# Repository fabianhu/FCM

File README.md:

FCM
===

FCM Flight Controller Firmware

Contents:

	Bootloader - the bootloader AVR32 project
	
	doc -  the main documentation folder -> read FCM Manual.pdf.
	
	hardware - here are the hardware sources. "hexa2wide" is our board. The actual physically produced board is under versions. This is the next release!
	
	software - the FCM copter control firmware main project

Size & weight:

	45 x 27 x 8 mm
	10 g

CPU:

	AVR32 UC3B0256
	32 bit
	48MHz

Sensors:

	Gyroscope (3 axis)
	Accelometer (3 axis)
	Magnetometer (3 axis)
	Barometer

Interfaces:

	4x PPM input or
	Receiver serial input for SPEKTRUM and HoTT or
	Receiver PPM sum signal input
	2x extra TTL USART (for Bluetooth, GPS, Telemetry etc.)
	6x PPM output for speed controllers (SimonK firmware recommended)
	optocoupler for 5 PPM outputs (placement variant)
	Pulse input for ultrasonic distance measurement
	USB for configuration and updates

Software features:

	FabOS32 RTOS
	Quaternion based attitude control
	Altitude hold
	Any copter configuration via mixing matrix
	RC compatibility
	HoTT SUMD receiver signal
	SPEKTRUM sattelite receiver signal
	4-channel "any RX" classic mode
	PPM sum signal
	USB Bootloader
	GPS integration with waypoint processing and return-to-home
	Throw to start
	
Telemetry

	HoTT telemetry with settings menue
	Bluetooth telemetry with settings menue, Attitude and graph display
	MAVlink prepared
	PID setting via extra RC analog channels

Software is "closed source" = all own code with minor extensions with LGPL
	Software is now open-sourced under GPL V3

Visit also the projects:
	FCM-android and
	FCM-Manager

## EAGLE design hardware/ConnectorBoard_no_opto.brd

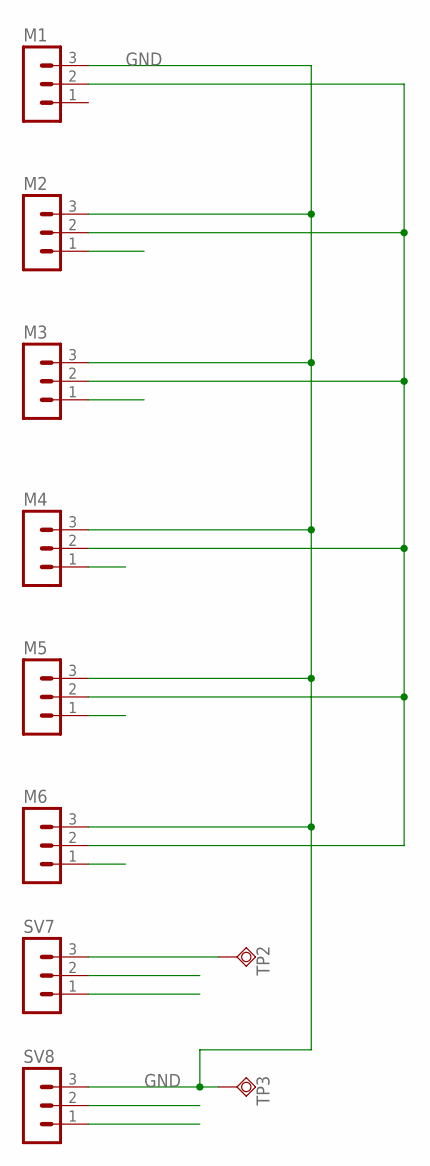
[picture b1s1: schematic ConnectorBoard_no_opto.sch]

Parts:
M1, M2, M3, M4, M5, M6: MA03-1
SV7, SV8: MA03-1
TP2, TP3: TPSQTP14SQ; TP14SQ

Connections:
GND: M1.3, M2.3, M3.3, M4.3, M5.3, M6.3, SV8.3, TP3.TP
unnamed: M1.2, M2.2, M3.2, M4.2, M5.2, M6.2
unnamed: SV7.3, TP2.TP

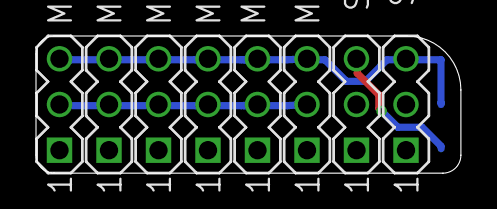
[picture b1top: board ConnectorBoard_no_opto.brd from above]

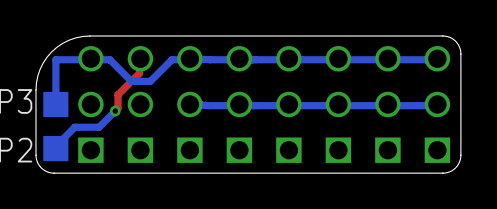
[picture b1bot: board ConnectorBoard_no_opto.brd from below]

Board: 2 copper layers, 23.6 x 7.6 mm, 10 parts (2 on the bottom side), 3 nets.

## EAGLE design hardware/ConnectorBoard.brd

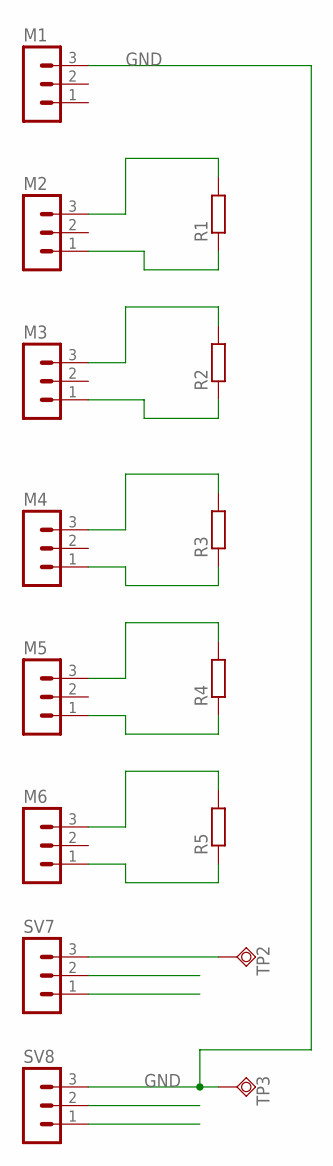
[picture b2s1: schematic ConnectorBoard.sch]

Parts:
M1, M2, M3, M4, M5, M6: MA03-1
R1, R2, R3, R4, R5: R-EU_R0402; R0402
SV7, SV8: MA03-1
TP2, TP3: TPSQTP14SQ; TP14SQ

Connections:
GND: M1.3, SV8.3, TP3.TP
unnamed: M3.3, R2.2
unnamed: M2.3, R1.2
unnamed: M2.1, R1.1
unnamed: M3.1, R2.1
unnamed: M4.3, R3.2
unnamed: M4.1, R3.1
unnamed: M5.3, R4.2
unnamed: M5.1, R4.1
unnamed: M6.3, R5.2
unnamed: M6.1, R5.1
unnamed: SV7.3, TP2.TP

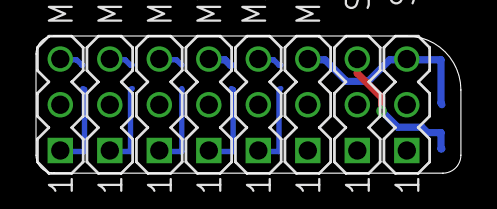
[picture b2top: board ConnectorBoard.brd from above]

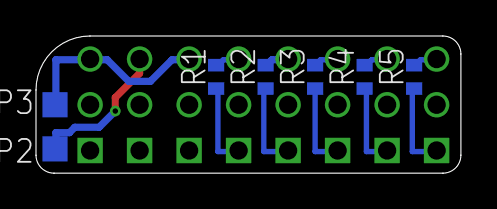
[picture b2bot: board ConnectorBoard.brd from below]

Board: 2 copper layers, 23.6 x 7.6 mm, 15 parts (7 on the bottom side), 12 nets.

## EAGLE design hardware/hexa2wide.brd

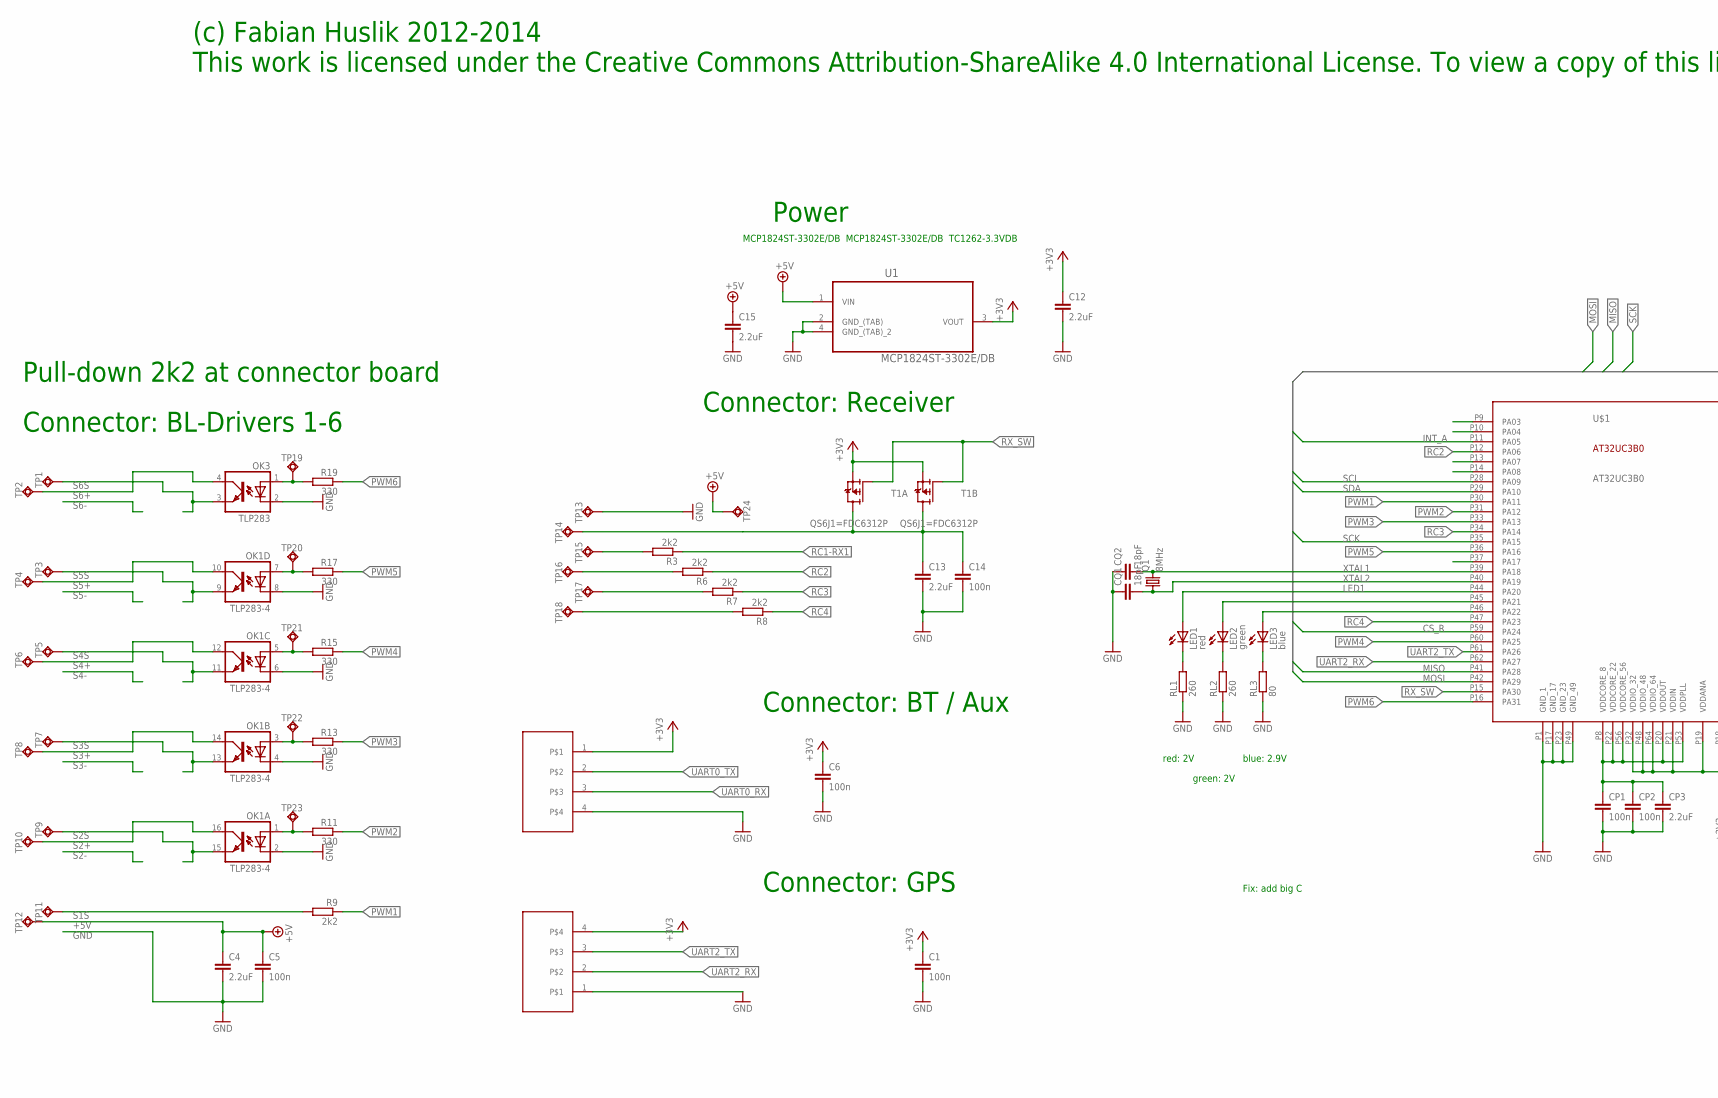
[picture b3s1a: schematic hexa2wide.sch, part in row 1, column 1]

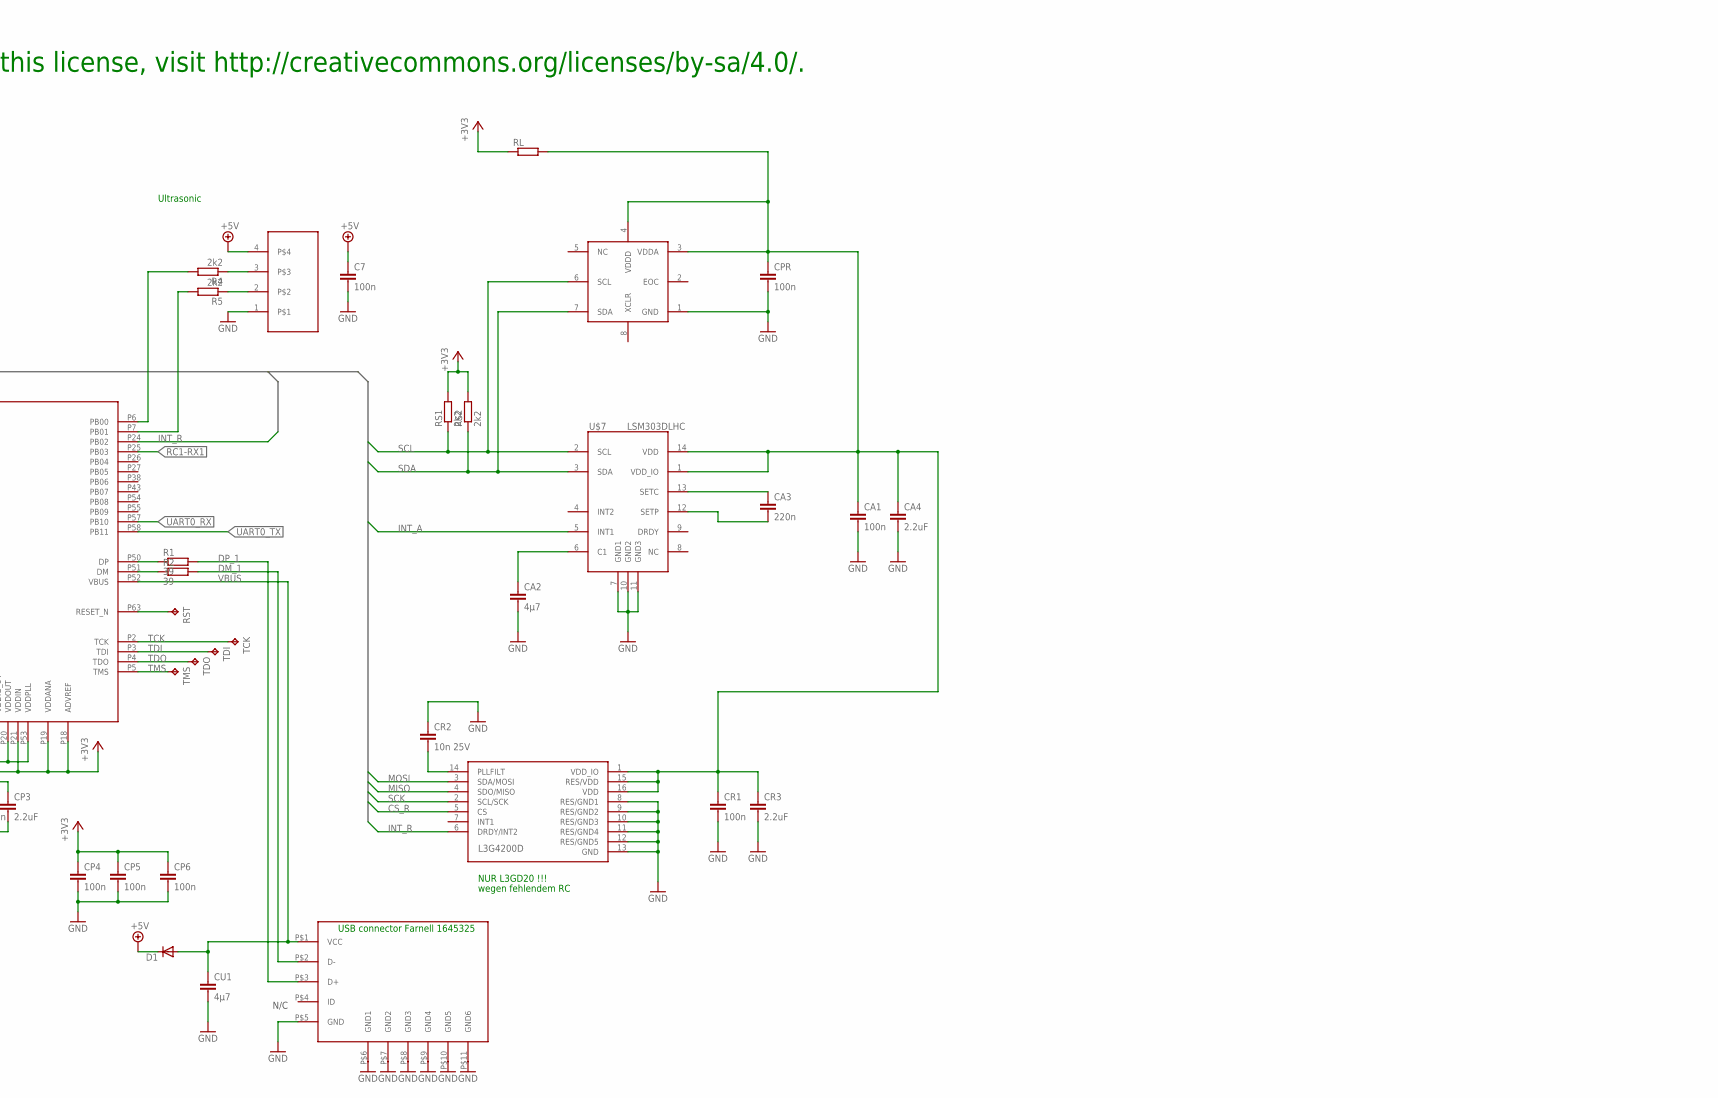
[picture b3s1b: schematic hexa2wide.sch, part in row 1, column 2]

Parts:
C1, C5, C6, C7, C14: 100n; C0402; MPN MCCA000050
C4, C12, C13, C15: 2.2uF; C0603K; MPN GRM188R61C225KE15D
CA1: 100n; C0402; MPN MCCA000050
CA2: 4µ7; C0805; MPN GRM219R61C475KE15D
CA3: 220n; C0402; MPN C0402C224K9PACTU
CA4: 2.2uF; C0603K; MPN GRM188R61C225KE15D
CP1, CP2, CP4, CP5, CP6: 100n; C0402; MPN MCCA000050
CP3: 2.2uF; C0603K; MPN GRM188R61C225KE15D
CPR: 100n; C0402; MPN MCCA000050
CQ1, CQ2: 18pF; C0402; MPN C0402C180J5GACTU
CR1: 100n; C0402; MPN MCCA000050
CR2: 10n 25V; C0402; MPN MCCA000076
CR3: 2.2uF; C0603K; MPN GRM188R61C225KE15D
CU1: 4µ7; C0805; MPN GRM219R61C475KE15D
D1: DIODE-MICROMELF-R; MICROMELF-R
LED1: red; CHIP-LED0603; MPN ASMT-RR45-AQ902
LED2: green; CHIP-LED0603; MPN ASMT-RF45-AN002
LED3: blue; CHIP-LED0603; MPN SMLE12BC7TT86Q
OK1: TLP283-4; MINI-FLAT-16; MPN ACPL-247-500E
OK3: TLP283; MINI-FLAT-4; MPN ACPL-217-500E
Q1: 8MHz; CTS406; MPN ABMM2-8.000MHZ-E2-T
R1, R2: 39; R0402; MPN CRCW040239R0FKEAHP
R3, R4, R5, R6, R7, R8, R9: 2k2; R0402; MPN CRCW040210K5FKED
R11, R13, R15, R17, R19: 330; R0402; MPN MCMR04X331 JTL
RL: R-EU_R0603; R0603; MPN 74279266
RL1, RL2: 260; R0402; MPN CRCW0402604RFKED
RL3: 80; R0402; MPN ERJ2RKF8062X
RS1, RS2: 2k2; R0402; MPN CRCW040210K5FKED
RST: TPB1,27; B1,27
T1: QS6J1=FDC6312P; SUPERSOT-6; MPN FDC6312P
TCK: TPB1,27; B1,27
TDI: TPB1,27; B1,27
TDO: TPB1,27; B1,27
TMS: TPB1,27; B1,27
TP1, TP2, TP3, TP4, TP5, TP6, TP7, TP8, TP9, TP10, TP11, TP12, TP13, TP14, TP15, TP16, TP17, TP18: TPSQTP16SQ; TP16SQ
TP19, TP20, TP21, TP22, TP23, TP24: TPSQTP10SQ; TP10SQ
U1: MCP1824ST-3302E/DB; SOT230P700X180-4N; MPN MCP1824ST-3302E/DB
U$1: AT32UC3B0; JEDEC_MS-026; MPN AT32UC3B0256-A2UT
U$4: UBB_MICRO_HIROSE; USB_MICRO; MPN ZX62-B-5PA(11)
U$5: L3G4200DHAND; LGA16_HAND; MPN L3GD20
U$7: LSM303HAND; LGA14_HAND; MPN LSM303DLHC
U$9: BMP085
U$10, U$11, U$12: 4WIRE_CONN; 4WIRE_PIN

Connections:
1V6: CP1.1, CP2.1, CP3.1, U$1.P8 (VDDCORE_8), U$1.P20 (VDDOUT), U$1.P22 (VDDCORE_22), U$1.P53 (VDDPLL), U$1.P56 (VDDCORE_56)
+3V3: C1.1, C6.1, C12.1, CP4.1, CP5.1, CP6.1, RL.1, RS1.2, RS2.2, T1.P$2 (S), T1.P$5 (S), U1.3 (VOUT), U$1.P18 (ADVREF), U$1.P19 (VDDANA), U$1.P21 (VDDIN), U$1.P32 (VDDIO_32), U$1.P48 (VDDIO_48), U$1.P64 (VDDIO_64), U$10.4, U$11.1
+5V: C4.1, C5.1, C7.1, C15.1, D1.C, TP12.TP, TP24.TP, U1.1 (VIN), U$12.4
CS_R: U$1.P59 (PA24), U$5.5 (CS)
DM: R2.1, U$1.P51 (DM)
DM_1: R2.2, U$4.P$2 (D-)
DP: R1.1, U$1.P50 (DP)
DP_1: R1.2, U$4.P$3 (D+)
GND: C1.2, C4.2, C5.2, C6.2, C7.2, C12.2, C13.2, C14.2, C15.2, CA1.2, CA2.2, CA4.2, CP1.2, CP2.2, CP3.2, CP4.2, CP5.2, CP6.2, CPR.2, CQ1.1, CQ2.1, CR1.2, CR2.1, CR3.2, CU1.2, OK1.2 (C), OK1.4 (C), OK1.6 (C), OK1.8 (C), OK3.2 (C), RL1.1, RL2.1, RL3.1, TP13.TP, U1.2 (GND_(TAB)), U1.4 (GND_(TAB)_2), U$1.P1 (GND_1), U$1.P17 (GND_17), U$1.P23 (GND_23), U$1.P49 (GND_49), U$4.P$5 (GND), U$4.P$6 (GND1), U$4.P$7 (GND2), U$4.P$8 (GND3), U$4.P$9 (GND4), U$4.P$10 (GND5), U$4.P$11 (GND6), U$5.8 (RES/GND1), U$5.9 (RES/GND2), U$5.10 (RES/GND3), U$5.11 (RES/GND4), U$5.12 (RES/GND5), U$5.13 (GND), U$7.7 (GND1), U$7.10 (GND2), U$7.11 (GND3), U$9.1 (GND), U$10.1, U$11.4, U$12.1
INT_A: U$1.P11 (PA05), U$7.5 (INT1)
INT_R: U$1.P24 (PB02), U$5.6 (DRDY/INT2)
LED1: LED1.A, U$1.P44 (PA20)
MISO: U$1.P41 (PA28), U$5.4 (SDO/MISO)
MOSI: U$1.P42 (PA29), U$5.3 (SDA/MOSI)
unnamed: LED1.C, RL1.2
unnamed: RST.TP, U$1.P63 (RESET_N)
unnamed: CA3.1, U$7.13 (SETC)
unnamed: LED2.C, RL2.2
unnamed: LED3.C, RL3.2
unnamed: LED2.A, U$1.P45 (PA21)
unnamed: LED3.A, U$1.P46 (PA22)
unnamed: CR2.2, U$5.14 (PLLFILT)
unnamed: CA2.1, U$7.6 (C1)
unnamed: CA3.2, U$7.12 (SETP)
unnamed: R3.2, TP15.TP
unnamed: C13.1, C14.1, T1.P$4 (D), T1.P$6 (D), TP14.TP
unnamed: R6.2, TP16.TP
unnamed: R7.2, TP17.TP
unnamed: R8.2, TP18.TP
unnamed: OK1.1 (A), R11.2, TP23.TP
unnamed: OK1.3 (A), R13.2, TP22.TP
unnamed: OK1.5 (A), R15.2, TP21.TP
unnamed: R4.1, U$12.3
unnamed: R5.1, U$12.2
unnamed: OK1.7 (A), R17.2, TP20.TP
unnamed: OK3.1 (A), R19.2, TP19.TP
PWM1: R9.1, U$1.P30 (PA11)
PWM2: R11.1, U$1.P31 (PA12)
PWM3: R13.1, U$1.P33 (PA13)
PWM4: R15.1, U$1.P60 (PA25)
PWM5: R17.1, U$1.P36 (PA16)
PWM6: R19.1, U$1.P16 (PA31)
RC1-RX1: R3.1, U$1.P25 (PB03)
RC2: R6.1, U$1.P12 (PA06)
RC3: R7.1, U$1.P34 (PA14)
RC4: R8.1, U$1.P47 (PA23)
RX_SW: T1.P$1 (G), T1.P$3 (G), U$1.P15 (PA30)
S1S: R9.2, TP11.TP
S2+: OK1.16 (COL), TP10.TP
S2S: OK1.15 (EMIT), TP9.TP
S3+: OK1.14 (COL), TP8.TP
S3S: OK1.13 (EMIT), TP7.TP
S4+: OK1.12 (COL), TP6.TP
S4S: OK1.11 (EMIT), TP5.TP
S5+: OK1.10 (COL), TP4.TP
S5S: OK1.9 (EMIT), TP3.TP
S6+: OK3.4 (COL), TP2.TP
S6S: OK3.3 (EMIT), TP1.TP
SCK: U$1.P35 (PA15), U$5.2 (SCL/SCK)
SCL: RS1.1, U$1.P28 (PA09), U$7.2 (SCL), U$9.6 (SCL)
SDA: RS2.1, U$1.P29 (PA10), U$7.3 (SDA), U$9.7 (SDA)
TCA0: R4.2, U$1.P6 (PB00)
TCB0: R5.2, U$1.P7 (PB01)
TCK: TCK.TP, U$1.P2 (TCK)
TDI: TDI.TP, U$1.P3 (TDI)
TDO: TDO.TP, U$1.P4 (TDO)
TMS: TMS.TP, U$1.P5 (TMS)
UART0_RX: U$1.P57 (PB10), U$11.3
UART0_TX: U$1.P58 (PB11), U$11.2
UART2_RX: U$1.P62 (PA27), U$10.2
UART2_TX: U$1.P61 (PA26), U$10.3
VBUS: CU1.1, D1.A, U$1.P52 (VBUS), U$4.P$1 (VCC)
VCCSENS: CA1.1, CA4.1, CPR.1, CR1.1, CR3.1, RL.2, U$5.1 (VDD_IO), U$5.15 (RES/VDD), U$5.16 (VDD), U$7.1 (VDD_IO), U$7.14 (VDD), U$9.3 (VDDA), U$9.4 (VDDD)
XTAL1: CQ2.2, Q1.3 (2), U$1.P39 (PA18)
XTAL2: CQ1.2, Q1.1, U$1.P40 (PA19)

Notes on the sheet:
USB connector Farnell 1645325
Connector: Receiver
Connector: BL-Drivers 1-6
Power
Connector: GPS
N/C
NUR L3GD20 !!!
wegen fehlendem RC
Connector: BT / Aux
Ultrasonic
MCP1824ST-3302E/DB MCP1824ST-3302E/DB TC1262-3.3VDB
red: 2V
green: 2V
blue: 2.9V
Pull-down 2k2 at connector board
Fix: add big C
This work is licensed under the Creative Commons Attribution-ShareAlike 4.0 International License. To view a copy of this license, visit http://creativecommons.org/licenses/by-sa/4.0/.
(c) Fabian Huslik 2012-2014

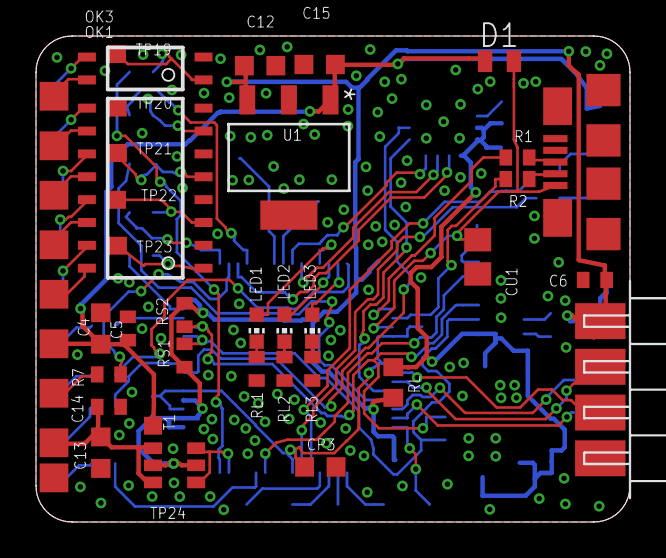
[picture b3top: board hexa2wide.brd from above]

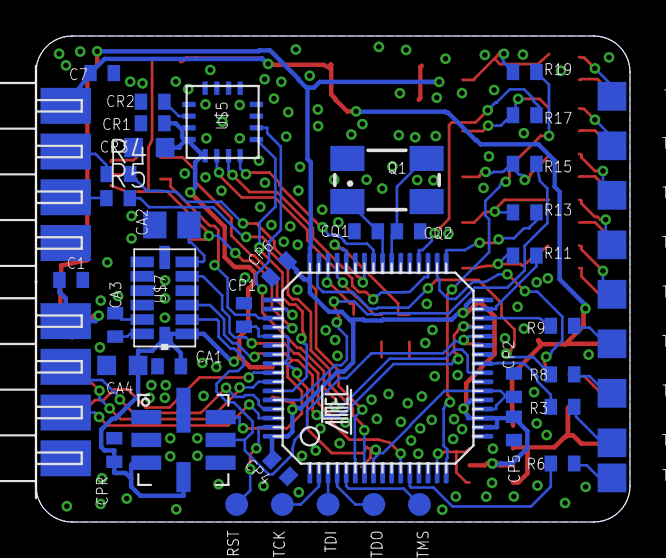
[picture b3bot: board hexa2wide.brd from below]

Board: 2 copper layers, 33.0 x 27.0 mm, 92 parts (49 on the bottom side), 75 nets.

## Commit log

2014-11-12 added the whole project.
2014-11-12 added hw versions and de-automatized versioning
2014-11-13 worked on sim
2014-11-13 worked on...
2014-11-15 worked on
2014-11-16 worked on, basic sim working
2014-11-20 falling down now
2014-11-20 simulation kinda running
2014-11-21 sim working in rudimentary mode
2014-11-25 nav adjustments for h gov
2014-11-25 stuff
2014-11-26 fix sim aerodynamic resistance error
    keep a build error on purpose, fix next time.
2014-11-28 fix switch over between modes
2014-11-28 fixed wrong direction of nav governor
2014-11-29 cleanup vector.c
2014-11-29 fixed som rotational problems and H-governor switch
2014-11-29 NAV working now in sim.
    changed PID scaling; new nav parameters,
    NAV working now in sim.
2014-11-30 implement sensor simulation
2014-11-30 avoid going down far away from home at RTH+ Display the simulated orientation
2014-11-30 renamed stuff
2014-11-30 push tag
2014-12-02 testing some algos
2014-12-04 do aerodynamics in vehicle frame
2014-12-05 add disturbance code
2014-12-06 fixed disturbance
2014-12-07 add rotation disturbance.
2014-12-07 cleanup
2014-12-08 fix disturbance bug
2014-12-08 fix stuff
2014-12-09 fix more stuff
2014-12-11 fixme fighting
2014-12-26 improve filtering - to be tested
2014-12-27 further fiddle around
2014-12-27 further debugging
2014-12-30 basic simulation running again, gyro simulation delivers implausible values right before liftoff.
2015-01-01 remove velocity
2015-01-01 remove slowspeed
2015-01-04 up DATE
2015-01-08 some cleanup
2015-01-11 fusion seems to work - to be tested with delayed GPS and baro
2015-01-11 switch on the sensor fusion ....
2015-01-12 fix the vector rotation
2015-01-19 quaternion vector rotation not working
2015-02-01 loads oft testcases
2015-02-01 some corrections
2015-02-01 minor corr
2015-02-11 Revert "some corrections"
    This reverts commit a371bd67a5920ac6f6e5a271a302a40648084823.
2015-02-13 re-mobilize stuff (remove testing stuff)
2015-02-13 working again
2015-02-15 more living than dead
2015-02-19 reverted some stuff, now it behaves correctly.
2015-03-07 nav working again (sim)
2015-03-08 fix comment
2015-03-16 test delay by 4
2015-03-17 fix simulation with GPS delay.
2015-04-12 make filtered stuff static
2015-04-21 updated and fixed nav governor with filter, which kills about 400ms of GPS delay.
2015-04-21 update version
2015-04-22 mini cleanup
2015-04-22 added GIT versionning (basic!)
2015-04-24 optimized version numbering
2015-04-24 updated default dataset
2015-04-24 prepare for fly
2015-04-25 fixed nav info
2015-04-26 added error terms
2015-05-14 added low pass code
2015-05-15 move filter code to governing.h
2015-05-17 minor changes
2015-05-20 fixed h startup + parameters
    fixed h reset to 0 at start
2015-05-20 updated default pars
2015-06-14 new parset / sim working
2015-06-18 minor cleanup
2015-07-09 add NAV text info
2015-07-11 fix signedness
2015-07-13 improved rad to degrees calculation and debug display
2015-08-02 updated diag stuff
2015-08-23 flight test
2015-09-16 add autobuild script
2015-09-16 create autobuild branch
2015-09-16 autobuild 16.09.2015 17:09
2015-09-16 autobuild 16.09.2015 17:17
2015-09-16 autobuild 16.09.2015 17:19
2015-09-16 update autobuild
2015-09-16 re run
